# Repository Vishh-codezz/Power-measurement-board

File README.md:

# Power-measurement-board
Developed a board that seamlessly integrates the current, voltage, ADC sensors, Bluetooth low energy as a data processor and transmitter, enabling wireless communication and mobile application that supplies real time power data, historical analysis, and graphical visualization allowing users to monitor and optimize energy consumption.

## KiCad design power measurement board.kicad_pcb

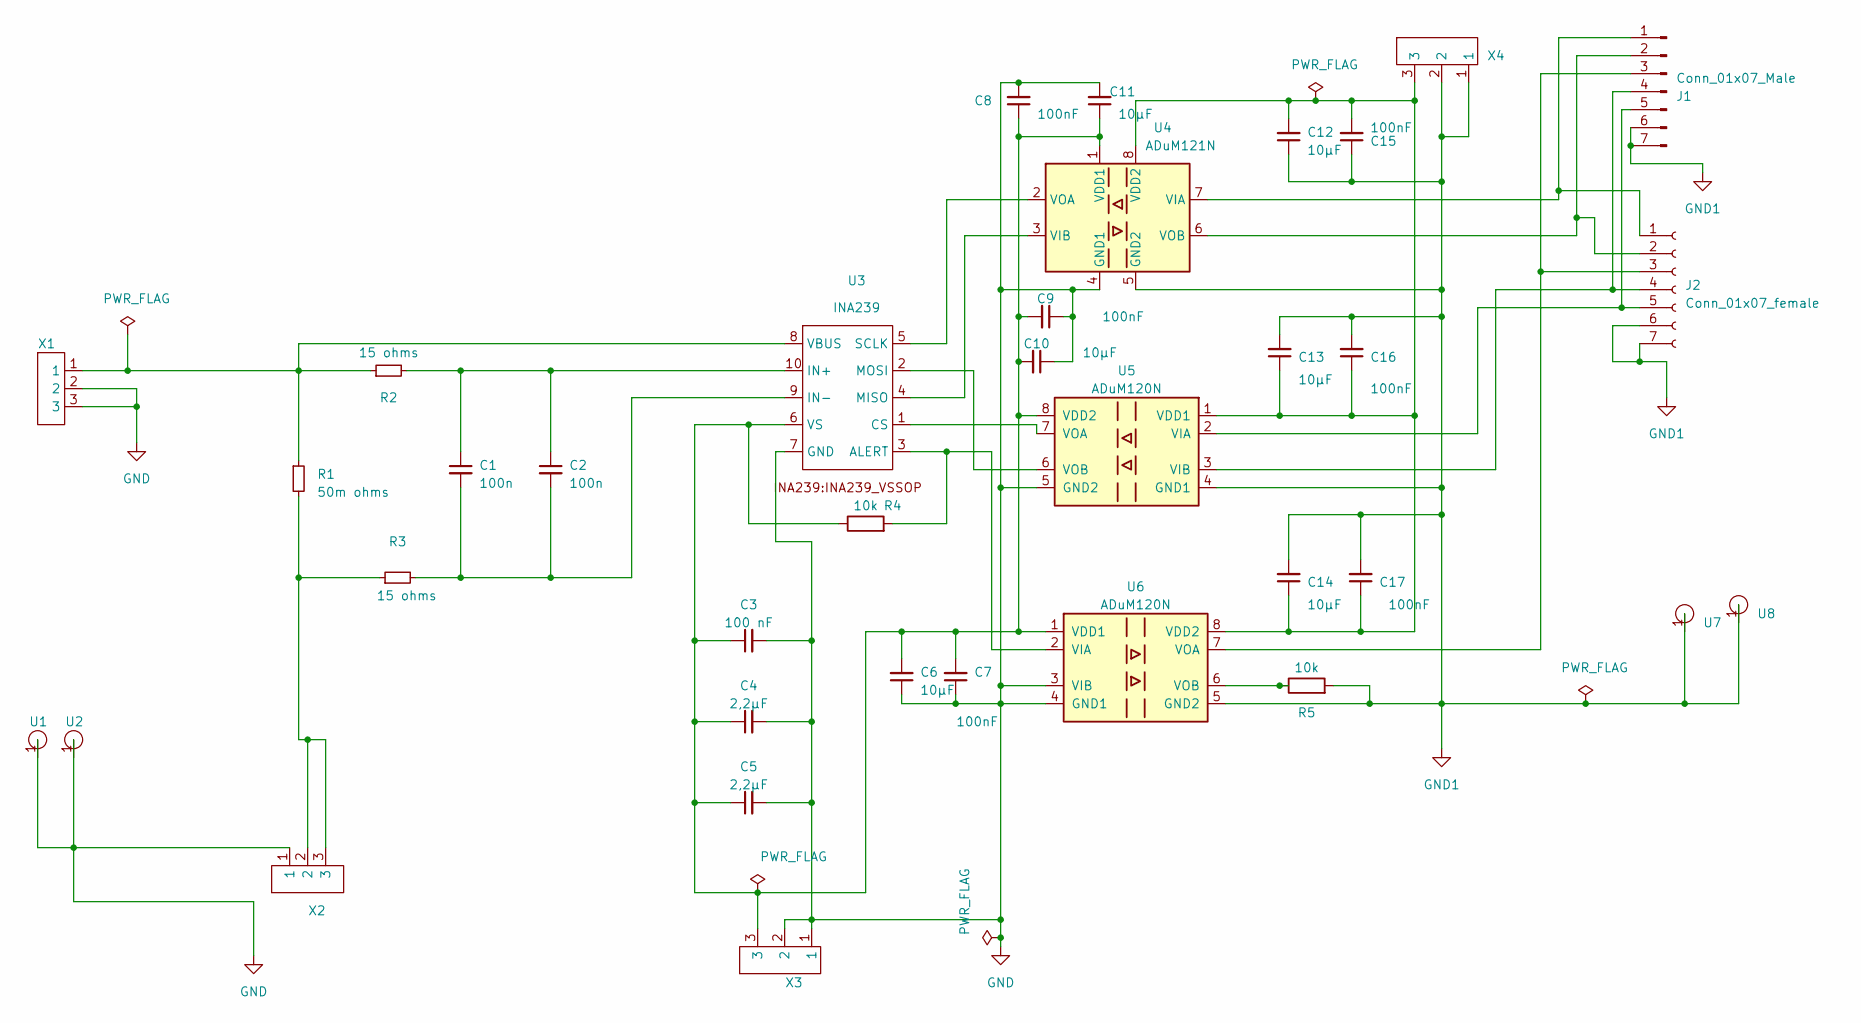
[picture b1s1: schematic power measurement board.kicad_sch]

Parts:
C1, C2: 100n; C_0402_1005Metric_Pad0.74x0.62mm_HandSolder
C3: 100 nF; C_0805_2012Metric_Pad1.18x1.45mm_HandSolder
C4, C5: 2,2μF; C_1206_3216Metric_Pad1.33x1.80mm_HandSolder
C6, C11, C12, C13: 10μF; C_1206_3216Metric_Pad1.33x1.80mm_HandSolder
C7, C9, C16, C17: 100nF; C_0402_1005Metric_Pad0.74x0.62mm_HandSolder
C8, C15: 100nF; C_1206_3216Metric_Pad1.33x1.80mm_HandSolder
C10, C14: 10μF; C_0402_1005Metric_Pad0.74x0.62mm_HandSolder
J1: Conn_01x07_Male; PinSocket_1x07_P2.54mm_Vertical
J2: Conn_01x07_female; PinHeader_1x07_P2.54mm_Vertical
R1: 50m ohms; R_2010_5025Metric_Pad1.40x2.65mm_HandSolder
R2, R3: 15 ohms; R_0402_1005Metric_Pad0.72x0.64mm_HandSolder
R4, R5: 10k; R_0402_1005Metric_Pad0.72x0.64mm_HandSolder
U1, U2, U7, U8: Soldernail
U3: INA239
U4: ADuM121N; SOIC-8_3.9x4.9mm_P1.27mm
U5, U6: ADuM120N; SOIC-8_3.9x4.9mm_P1.27mm
X1, X2, X3, X4: AKL073-03_footprint

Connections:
GND: C3.2, C4.2, C5.2, C6.1, C7.1, C8.2, C9.1, C10.1, C11.2, U1.1, U2.1, U3.7 (GND), U4.4 (GND1), U5.5 (GND2), U6.3 (VIB), U6.4 (GND1), X1.2, X1.3, X2.1, X3.1, X3.2
GND1: C12.1, C13.2, C14.2, C15.1, C16.2, C17.2, J1.6, J1.7, J2.6, J2.7, R5.2, U4.5 (GND2), U5.4 (GND1), U6.5 (GND2), U7.1, U8.1, X4.1, X4.2
unnamed: J1.1, J2.1, U4.7 (VIA)
unnamed: J1.2, J2.2, U4.6 (VOB)
unnamed: J1.3, J2.3, U6.7 (VOA)
unnamed: J1.4, J2.4, U5.3 (VIB)
unnamed: J1.5, J2.5, U5.2 (VIA)
unnamed: R1.2, R3.1, X2.2, X2.3
unnamed: R4.2, U3.3 (ALERT), U6.2 (VIA)
unnamed: U3.1 (CS), U5.7 (VOA)
unnamed: C1.1, C2.1, R2.2, U3.10 (IN+)
unnamed: C1.2, C2.2, R3.2, U3.9 (IN-)
unnamed: U3.4 (MISO), U4.3 (VIB)
unnamed: U3.2 (MOSI), U5.6 (VOB)
unnamed: U3.5 (SCLK), U4.2 (VOA)
unnamed: R1.1, R2.1, U3.8 (VBUS), X1.1
unnamed: C12.2, C13.1, C14.1, C15.2, C16.1, C17.1, U4.8 (VDD2), U5.1 (VDD1), U6.8 (VDD2), X4.3
unnamed: R5.1, U6.6 (VOB)
pwr: C3.1, C4.1, C5.1, C6.2, C7.2, C8.1, C9.2, C10.2, C11.1, R4.1, U3.6 (VS), U4.1 (VDD1), U5.8 (VDD2), U6.1 (VDD1), X3.3

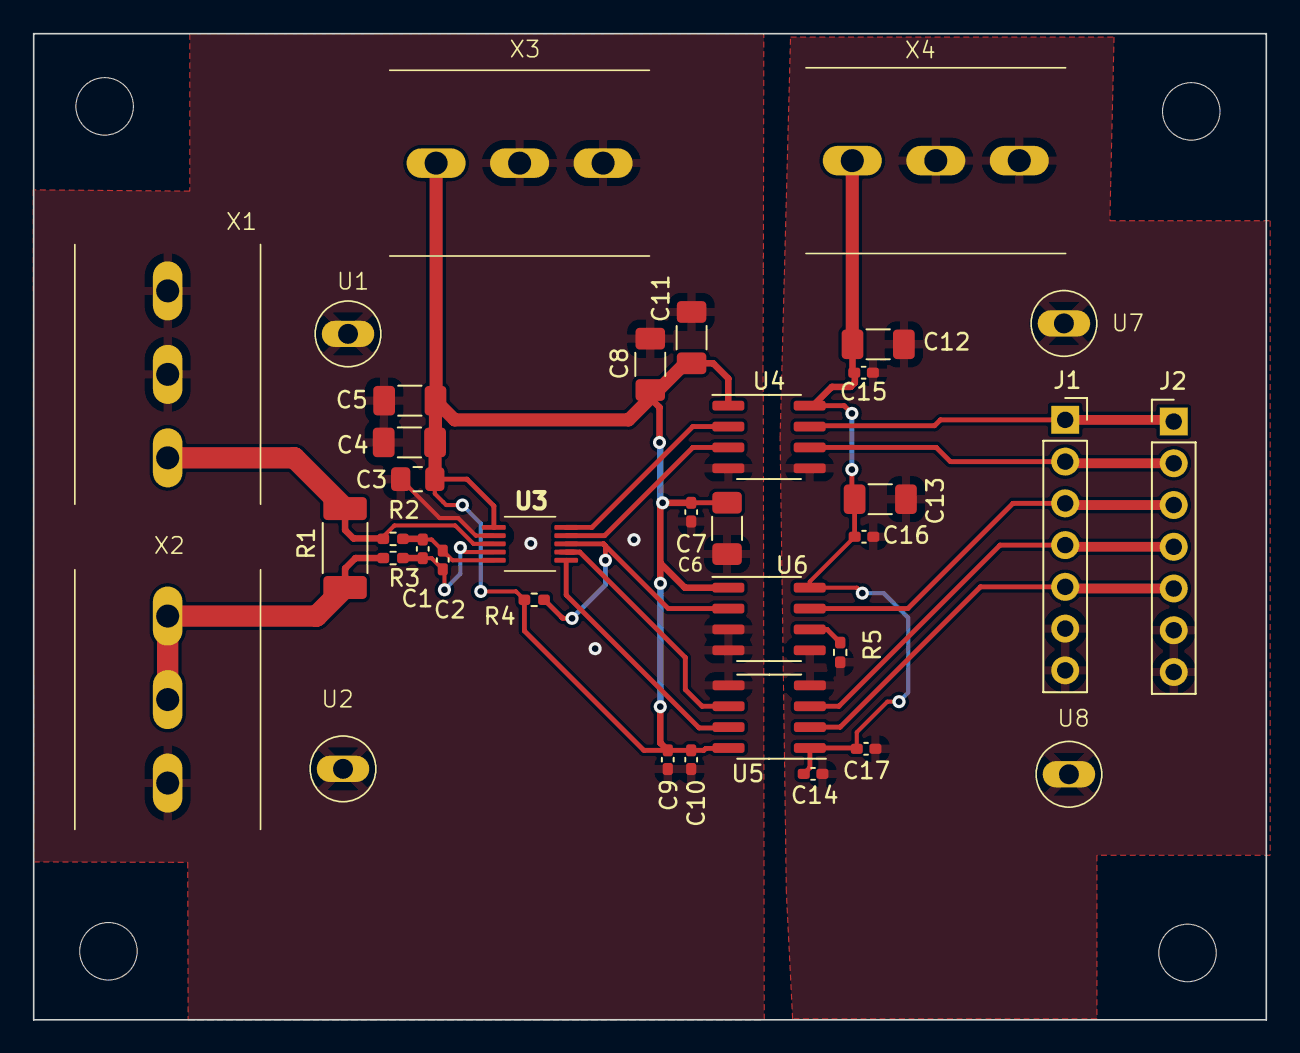
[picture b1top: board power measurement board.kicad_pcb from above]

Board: 2 copper layers, 75.0 x 60.0 mm, 40 parts (0 on the bottom side), 19 nets.

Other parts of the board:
hole, hole1, hole2, hole3: MountingHole_3.5mm
